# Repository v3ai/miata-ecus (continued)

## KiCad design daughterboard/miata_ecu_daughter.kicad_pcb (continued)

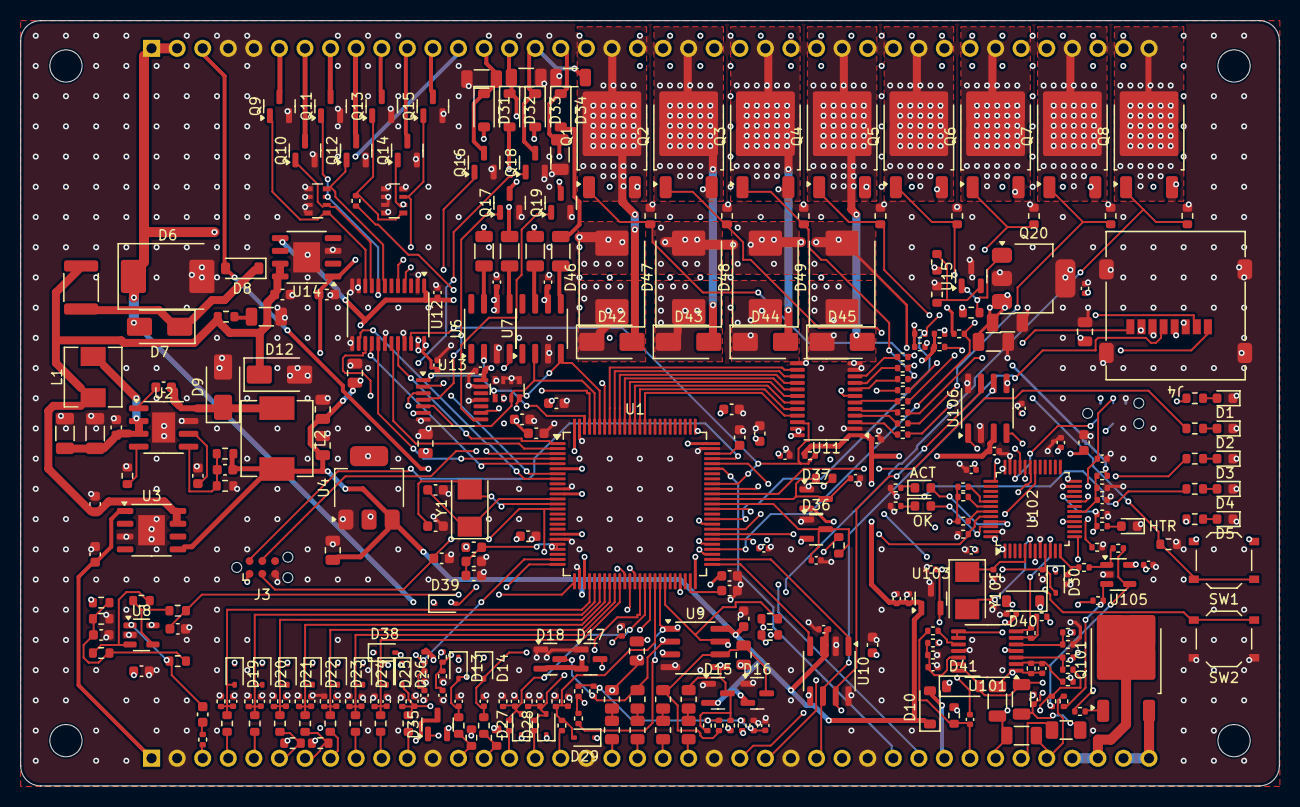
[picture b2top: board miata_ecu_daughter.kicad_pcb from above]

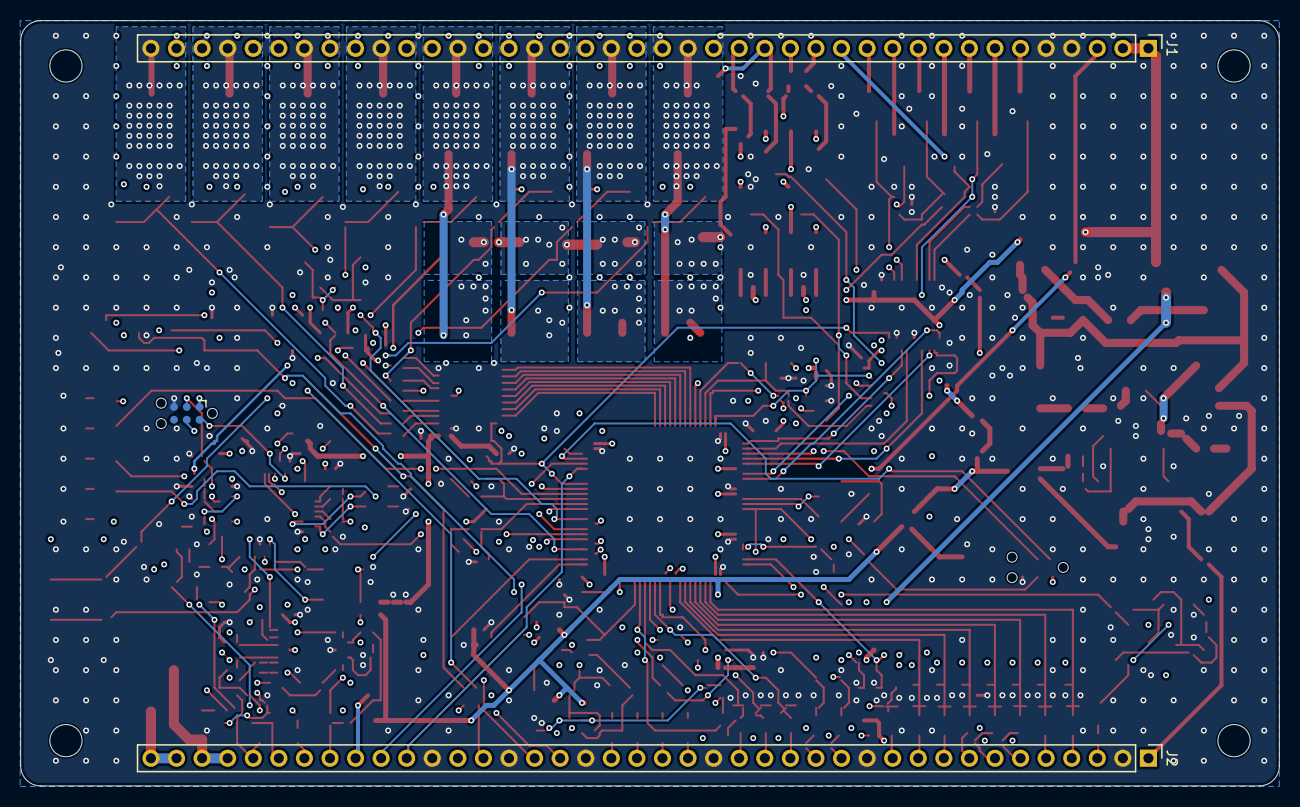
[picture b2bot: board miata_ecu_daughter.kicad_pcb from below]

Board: 6 copper layers, 125.0 x 76.0 mm, 338 parts (3 on the bottom side), 230 nets.

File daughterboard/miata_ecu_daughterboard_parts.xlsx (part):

Group | Qty | Value | Description | Designators | Footprint | LCSC # | JLC type | Notes | Manufacturer | MPN
MCU & support
MCU & support | 7 | 100n |  | C1, C2, C3, C5, C6, C12, C15 | C_0603_1608Metric | C14663 | Basic |  | YAGEO | CC0603KRX7R9BB104
MCU & support | 1 | 100n |  | C4 | C_0402_1005Metric | C1525 | Basic |  | Samsung Electro-Mechanics | CL05B104KO5NNNC
MCU & support | 1 | 10k |  | R1 | R_0603_1608Metric | C25804 | Basic |  | UNI-ROYAL(Uniroyal Elec) | 0603WAF1002T5E
MCU & support | 1 | 1u |  | C11 | C_0603_1608Metric | C15849 | Basic |  | Samsung Electro-Mechanics | CL10A105KB8NNNC
MCU & support | 2 | 2.2u |  | C9, C10 | C_0603_1608Metric | C23630 | Basic |  | Samsung Electro-Mechanics | CL10A225KO8NNNC
MCU & support | 2 | 33p |  | C13, C14 | C_0603_1608Metric | C1663 | Extended |  | Samsung Electro-Mechanics | CL10C330JB8NNNC
MCU & support | 2 | 4.7u |  | C7, C8 | C_0603_1608Metric | C19666 | Basic |  | Samsung Electro-Mechanics | CL10A475KO8NNNC
MCU & support | 1 | 8MHz | 8MHz crystal 5032, 20pF (YXC X50328MSB2GI) | Y1 | Crystal_SMD_5032-2Pin_5.0x3.2mm | C115962 | Extended |  | YXC Crystal Oscillators | X50328MSB2GI
MCU & support | 1 | BLM18PG221 |  | FB1 | L_0603_1608Metric | C80165 | Extended |  | Murata | BLM18PG221SN1D
MCU & support | 1 | BOOT |  | SW1 | SW_Push_1P1T_XKB_TS-1187A | C318884 | Basic |  | XKB Connection | TS-1187A-B-A-B
MCU & support | 1 | RESET |  | SW2 | SW_Push_1P1T_XKB_TS-1187A | C318884 | Basic |  | XKB Connection | TS-1187A-B-A-B
MCU & support | 1 | STM32F407VGT6 | MCU, Cortex-M4F 168MHz, 1MB flash, LQFP-100 | U1 | LQFP-100_14x14mm_P0.5mm | C12345 | Extended |  | STMicroelectronics | STM32F407VGT6
MCU & support | 1 | SWD | Tag-Connect TC2030-NL footprint, nothing to place | J3 | Tag-Connect_TC2030-IDC-NL_2x03_P1.27mm_Vertical |  |  | Not assembled
Status LEDs
Status LEDs | 5 | 1k |  | R2, R3, R4, R5, R6 | R_0603_1608Metric | C21190 | Basic |  | UNI-ROYAL(Uniroyal Elec) | 0603WAF1001T5E
Status LEDs | 1 | BLUE |  | D2 | LED_0603_1608Metric | C2288 | Extended |  | Hubei KENTO Elec | KT-0603B
Status LEDs | 2 | GREEN |  | D1, D5 | LED_0603_1608Metric | C12624 | Extended |  | Hubei KENTO Elec | KT-0603G
Status LEDs | 1 | RED |  | D4 | LED_0603_1608Metric | C2286 | Basic |  | Hubei KENTO Elec | KT-0603R
Status LEDs | 1 | YELLOW |  | D3 | LED_0603_1608Metric | C2287 | Extended |  | Hubei KENTO Elec | KT-0603Y
Power
Power | 1 | 1 |  | R7 | R_0603_1608Metric | C22936 | Basic |  | UNI-ROYAL(Uniroyal Elec) | 0603WAF100KT5E
Power | 1 | 100n |  | C19 | C_0603_1608Metric | C14663 | Basic |  | YAGEO | CC0603KRX7R9BB104
Power | 2 | 100n |  | C28, C29 | C_0402_1005Metric | C1525 | Basic |  | Samsung Electro-Mechanics | CL05B104KO5NNNC
Power | 1 | 10k |  | R8 | R_0603_1608Metric | C25804 | Basic |  | UNI-ROYAL(Uniroyal Elec) | 0603WAF1002T5E
Power | 1 | 10n |  | C20 | C_0603_1608Metric | C57112 | Basic |  | FH(Guangdong Fenghua Advanced Tech) | 0603B103K500NT
Power | 4 | 10u |  | C22, C23, C26, C27 | C_0805_2012Metric | C15850 | Basic |  | Samsung Electro-Mechanics | CL21A106KAYNNNE
Power | 3 | 10u/50V |  | C16, C17, C18 | C_1206_3216Metric | C13585 | Basic |  | Samsung Electro-Mechanics | CL31A106KBHNNNE
Power | 1 | 10uH |  | L2 | L_Sunlord_MWSA0603S | C132141 | Extended |  | Sunlord | MWSA0603S-100MT
Power | 1 | 12k |  | R10 | R_0603_1608Metric | C22790 | Basic |  | UNI-ROYAL(Uniroyal Elec) | 0603WAF1202T5E
Power | 2 | 1u |  | C24, C25 | C_0603_1608Metric | C15849 | Basic |  | Samsung Electro-Mechanics | CL10A105KB8NNNC
Power | 1 | 2.2uH |  | L1 | L_Sunlord_MWSA0503S | C177247 | Extended |  | cjiang (Changjiang Microelectronics Tech) | FXL0530-2R2-M
Power | 1 | 220p |  | C21 | C_0603_1608Metric | C1603 | Basic |  | Samsung Electro-Mechanics | CL10B221KB8NNNC
Power | 2 | 33k |  | R11, R13 | R_0402_1005Metric | C25779 | Basic |  | UNI-ROYAL(Uniroyal Elec) | 0402WGF3302TCE
Power | 2 | 6.8k |  | R12, R14 | R_0402_1005Metric | C25917 | Basic |  | UNI-ROYAL(Uniroyal Elec) | 0402WGF6801TCE
Power | 1 | 68k |  | R9 | R_0603_1608Metric | C23231 | Basic |  | UNI-ROYAL(Uniroyal Elec) | 0603WAF6802T5E
Power | 1 | B360A | 3A 60V Schottky, buck catch diode | D9 | D_SMA | C94193 | Extended |  | Diodes Incorporated | B360A-13-F
Power | 2 | B5819W | 1A 40V Schottky | D8, D10 | D_SOD-123 | C8598 | Extended |  | JSCJ | B5819W SL
Power | 1 | LDL1117S33R |  | U4 | SOT-223-3_TabPin2 | C435835 | Extended |  | STMicroelectronics | LDL1117S33R
Power | 1 | LMR14020 | 40V 2A buck converter, 12V -> 5V | U2 | SOIC-8-1EP_3.9x4.9mm_P1.27mm_EP2.29x3mm | C187824 | Extended |  | Texas Instruments | LMR14020SDDAR
Power | 1 | SMCJ30A | 1500W TVS, load dump | D6 | D_SMC | C224048 | Extended |  | Littelfuse | SMCJ30A
Power | 1 | SS34 | 3A 40V Schottky | D7 | D_SMA | C8678 | Basic |  | MDD(Microdiode Semiconductor) | SS34
Power | 1 | TLS115B0EJ | 5V sensor supply tracker, short-to-battery protected | U3 | Infineon_PG-DSO-8-27_3.9x4.9mm_EP2.65x3mm | C3743696 | Extended |  | Infineon | TLS115B0EJ
Injector / solenoid drivers
Injector / solenoid drivers | 1 | BCP53-16 |  | Q20 | SOT-223 | C85085 | Extended
Injector / solenoid drivers | 1 | VND14NV04 |  | Q101 | TO-252-2 | C2649436 | Extended |  | STMicroelectronics | VND14NV04TR-E
Injector / solenoid drivers | 8 | VND7NV04TR-E |  | Q1, Q2, Q3, Q4, Q5, Q6, Q7, Q8 | TO-252-2 | C155605 | Extended
Injector / solenoid drivers | 11 | ZXMS6004FFTA |  | Q9, Q10, Q11, Q12, Q13, Q14, Q15, Q16, Q17, Q18, Q19 | SOT-23 | C95063 | Extended
Ignition drivers
Ignition drivers | 4 | 100 |  | R15, R16, R17, R18 | R_1206_3216Metric | C17901 | Extended
Ignition drivers | 2 | 1u |  | C34, C35 | C_0402_1005Metric | C52923 | Extended |  | Samsung Electro-Mechanics | CL05A105KA5NQNC
Ignition drivers | 4 | 3.3k |  | R144, R145, R146, R147 | R_1206_3216Metric | C26032 | Extended
Ignition drivers | 1 | 4x10k |  | RN1 | R_Array_Convex_4x0603 | C29718 | Basic |  | UNI-ROYAL(Uniroyal Elec) | 4D03WGJ0103T5E
Ignition drivers | 1 | 74HCT04PW |  | U13 | TSSOP-14_4.4x5mm_P0.65mm | C131317 | Extended
Ignition drivers | 4 | B5819W | 1A 40V Schottky | D31, D32, D33, D34 | D_SOD-123 | C8598 | Extended |  | JSCJ | B5819W SL
Ignition drivers | 1 | BAT54WS |  | D39 | D_SOD-323 | C124205 | Extended |  | Diodes Incorporated | BAT54WS-7-F
Ignition drivers | 1 | Mezz_Power_Out | 1x40 2.54mm male header (power/outputs) | J1 | PinHeader_1x40_P2.54mm_Vertical | C2977586 | Extended |  | ZHOURI | 2.54-1*40
Ignition drivers | 2 | TC4427 | Dual 1.5A driver, 5V logic out for COP smart coils | U6, U7 | SOIC-8_3.9x4.9mm_P1.27mm | C20551 | Extended |  | Microchip | TC4427AEOA713
Knock input
Knock input | 3 | 100k |  | R45, R46, R47 | R_0603_1608Metric | C25803 | Basic |  | UNI-ROYAL(Uniroyal Elec) | 0603WAF1003T5E
Knock input | 1 | 100n |  | C44 | C_0603_1608Metric | C14663 | Basic |  | YAGEO | CC0603KRX7R9BB104
Knock input | 1 | 10k |  | R49 | R_0603_1608Metric | C25804 | Basic |  | UNI-ROYAL(Uniroyal Elec) | 0603WAF1002T5E
Knock input | 1 | 10n |  | C46 | C_0603_1608Metric | C57112 | Basic |  | FH(Guangdong Fenghua Advanced Tech) | 0603B103K500NT
Knock input | 1 | 1u |  | C45 | C_0603_1608Metric | C15849 | Basic |  | Samsung Electro-Mechanics | CL10A105KB8NNNC
Knock input | 1 | 2.2k |  | R138 | R_0402_1005Metric | C25879 | Basic |  | UNI-ROYAL | 0402WGF2201TCE
Knock input | 1 | 330 |  | R50 | R_0603_1608Metric | C23138 | Basic |  | UNI-ROYAL(Uniroyal Elec) | 0603WAF3300T5E
Knock input | 1 | 47k |  | R48 | R_0603_1608Metric | C25819 | Basic |  | UNI-ROYAL(Uniroyal Elec) | 0603WAF4702T5E
Knock input | 1 | LMV321IDBVR | Op-amp, knock sensor gain stage | U8 | SOT-23-5 | C7972 | Extended |  | Texas Instruments | LMV321IDBVR
VR (crank/cam) input
VR (crank/cam) input | 4 | 100k |  | R73, R74, R75, R76 | R_0402_1005Metric | C25741 | Extended |  | UNI-ROYAL(Uniroyal Elec) | 0402WGF1003TCE
VR (crank/cam) input | 1 | 100n |  | C60 | C_0402_1005Metric | C1525 | Basic |  | Samsung Electro-Mechanics | CL05B104KO5NNNC
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
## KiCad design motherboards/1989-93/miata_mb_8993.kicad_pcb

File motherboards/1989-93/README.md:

# Miata ECU motherboard 1989-1993 (NA6), rev 0.11

The motherboard replaces the stock Mazda ECU board inside the **stock ECU case**. It carries:

- the stock harness header;
- the year-independent I/O: the LSU 4.9 wideband sensor connector, IAT, USB-C and the MAP sensor;
- the sockets for the universal daughterboard, which does all the engine control (including the wideband controller).

## Changes in this revision
- Rev 0.11, for daughterboard rev 0.9: the throttle position sensor conversion uses the stock throttle switch plug, as rusEFI's Hellen NA6 and MRE boards do, instead of rev 0.10's separate lead: J6 is gone. Harness pin 1N (the manual cars' idle contact) is no longer wired straight to the sensor 5 V: it goes through R28 (0R, not fitted), so a car with the stock switch no longer shorts the 5 V to ground at every idle (rev 0.10 and earlier did, if 1N is the idle contact as the rusEFI sources say). Pin 2L goes through R29 (0R, fitted) to the spare analog AUX1 as before, or through R30 (0R, not fitted) to the TPS input. For a sensor on the stock plug: fit R28, move R29 to R30. The links are hand-routed into the rev 0.9 copper; nothing else moved.
- Rev 0.10 (replaced by 0.11): J6, a 4-pin connector for a separate TPS lead.
- Rev 0.9, for daughterboard rev 0.9: the daughterboard sits 16 mm lower, centred on the board (42 mm from the top, as up to rev 0.7), with its J1 on its top edge again: JD1 and the upper standoffs HD1/HD2 are back at their rev 0.7 places, JD2, the lower standoffs HD3/HD4, the AUX header J5 (with F4 beside it) and the parts placed against JD2 (CAN termination R1/R6, pull-up options) are 16 mm lower, and the board is routed again. Not compatible with a rev 0.8 daughterboard.
- Rev 0.8, for daughterboard rev 0.8: the harness's sensor 5 V (1N, 2K) and the AUX header pin J5-14 now come from the daughterboard's protected 5 V (V5_EXT, JD1 pin 13, which was a ground pin): a sensor 5 V wire shorted to the battery no longer back-feeds the MAP sensor and the ECU's own 5 V. The MAP sensor keeps its own supply (V5_SENS). The daughterboard outline on the silkscreen is 16 mm taller (125 x 76 mm): its new strip of output drivers overhangs the free area above JD1. D3/D4 (the batch injector clamps) are now SMCJ30A (33.3-36.8 V breakdown) instead of SMCJ40A: the new daughterboard drivers clamp at 40 V minimum, so a 40 V TVS could leave the turn-off energy in a driver; at 30 V the TVS always clamps first. Not-fitted option R27: 4.7k pull-up from the protected 5 V for the manual cars' TPS idle switch on 2L.
- Rev 0.7: LSU heater fuse F1 is a 3 A hold PTC (LUTE 2920L300/30GR, 30 V, 2920 size) instead of the 2 A 1812 part. A cold LSU 4.9 heater draws 1.6-2.3 A rms at the start of the wideband's warm-up, more than the old fuse holds once warm, so it could trip and the controller time out. No 1812 PTC holds 3 A above 8 V.
- Rev 0.6: freewheel diode D1 on the idle valve and D2 on the purge solenoid (2X) to its +12 V feed (the PWM turn-off energy no longer goes into the daughterboard driver); F4 resettable fuse on the AUX +12 V pin J5-15; not-fitted 12 V pull-up options R20-R22 for the VSS / A/C / clutch inputs. INJ1+INJ4 drive 2U and INJ2+INJ3 drive 2V in parallel (R23/R24), with an SMCJ40A clamp per wire (D3/D4), so no driver carries two injectors; 2Y/2Z are only reached through the not-fitted sequential-conversion links R25/R26.
- Rev 0.5: IAT source is now a removable jumper (JP1, 1x3 2.54 mm header + shunt) instead of the R4 / R5 0R links: shunt on EXT (default) reads the IAT connector J3, on STOCK the stock harness sensor; labelled on the silkscreen.
- Rev 0.4: MAP sensor is now the MPX5700AP (absolute, case 867B, one barb; LCSC C90152) instead of the MPX5700DP: new footprint with the real lozenge body and offset barb, holes on the NXP 23.11 mm spacing with 3.3 mm M3 clearance drills.
- Rev 0.3: sensor 5 V now on both 1N (NA6, per the Hellen NA6 map) and 2K; spare low side on 1R (the early cars' BLK/GRN fan-relay wire); 2S left open (it is only used on 94-95).
- Rev 0.2: wideband controller moved to the daughterboard; J5 centred; MAP sensor rotated 90 deg clockwise; LSU connector 6 mm right; SWD header removed; heater fuse now 30 V rated.

## Files
| Path | What |
|---|---|
| `miata_mb_8993.kicad_pro / .kicad_sch / .kicad_pcb` | KiCad 7 project. Root schematic plus three sheets: harness, daughterboard, I/O |
| `miata_mb_8993_schematic.pdf` | Schematic PDF |
| `fab/miata-ecu-motherboard-1989-93-rev0.11_jlcpcb_gerbers.zip`, `fab/miata-ecu-motherboard-1989-93-rev0.11_jlcpcb_bom.csv`, `fab/miata-ecu-motherboard-1989-93-rev0.11_jlcpcb_cpl.csv` | JLC fabrication and assembly files (2 layers, 1.6 mm). The JLC BOM is the SMD parts and USB-C only |
| `fab/miata-ecu-motherboard-1989-93-rev0.11_self_order_bom.csv` | Everything you order and fit yourself: harness header, through-hole connectors, MAP sensor, shunt, standoffs and screws, plus the not-fitted options. Its columns load into LCSC's BOM tool |
| `fab/miata-ecu-motherboard-1989-93-rev0.11_parts_list.csv` | Every part, including the hand-fitted and not-fitted ones |
| `fab/drc_report.txt` | KiCad DRC |
| `ecu_mb.pretty/`, `fp-lib-table` | Project footprints (harness header, MAP sensor lying flat, USB-C, M4 case hole) |
| `renders/` | Top and bottom copper |
| `scripts/` | The design source; `mb_make.sh` rebuilds the whole board |

## Case fit
Stock NA case (same for 1990-95). Outline and holes come from the rusEFI microRusEFI NA plug-and-play board, which fits this case, measured against its known 48-pin header footprint, and from the early Hellen NA6 KiCad board (rev a/b), which uses the same Mazda case outline. H1 is a recessed boss: stack 3 M4 washers under the board.

Board: **154.0 × 161.5 mm**, 1.6 mm. The origin is the top-left corner and y points down, toward the bottom edge.

| Hole | x, y (mm) |
|---|---|
| H1 | 17.0, 7.3 |
| H2 | 137.0, 7.3 |
| H3 | 4.0, 84.0 |
| H4 | 150.0, 84.0 |
| H5 | 4.0, 143.0 |
| H6 | 150.0, 143.0 |

All holes are 4.5 mm plated with a 7 mm pad, tied to GND, for M4 screws. Harness header terminal 1A sits at (39.70, 18.13) mm (lower pin row).

## Harness header
TE **174917-6**, 48 pins: plug 1 = 1A-1V (22 pins), plug 2 = 2A-2Z (26 pins); rusEFI's 1990 page calls the second plug 3A-3Z. TE lists it as not currently available: desolder one from a stock ECU or use a clone. Fitted by hand.

| Pin | Net | Use | Stock function / note |
|---|---|---|---|
| 1B | `VBAT_IN` | ECU power (main relay) | main relay output: ECU power |
| 1C | `VIGN_IN` | switched 12 V sense (wakes the logic supply) | starter (START) signal: battery only while cranking. Not ignition-on: the firmware doesn't use it as ignition sense |
| 1E | `OUT_CEL` | check engine lamp |  |
| 1G | `OUT_IGN1` | ignition 1 (5 V logic) | igniter 1&4 (wasted spark) / COP 1 |
| 1H | `OUT_IGN2` | ignition 2 (5 V logic) | igniter 2&3 (wasted spark) / COP 2 |
| 1J | `OUT_AC` | A/C relay | A/C relay |
| 1L | `OUT_FAN` | fan relay | radiator fan relay |
| 1M | `IN_SW1` | 12 V switch input 1 | vehicle speed sensor |
| 1N | `HARN_1N` |  | manual cars: the stock throttle switch's idle contact (closes to ground at idle). 5 V only through R28 (not fitted), for a 0-5 V sensor on the stock plug |
| 1Q | `IN_SW2` | 12 V switch input 2 | A/C switch |
| 1R | `OUT_LS7` | spare low side | A/C extra cooling fan relay (BLK/GRN) on 1990-91; moved to 1L on later cars |
| 1V | `IN_SW3` | 12 V switch input 3 | clutch switch |
| 2A | `GND` | ground |  |
| 2B | `GND` | ground | power ground |
| 2C | `GND` | ground |  |
| 2D | `GND` | ground | signal ground |
| 2E | `IN_HALL1` | hall input 1 (crank) | CAS crank (SGT, open collector) |
| 2F | `GND` | ground | AFM ground |
| 2G | `IN_HALL2` | hall input 2 (cam) | CAS cam (SGC) |
| 2I | `OUT_TACH` | tach out |  |
| 2K | `V5_EXT` | sensor 5 V reference (out; protected, short-to-battery proof) | 5 V sensor reference (protected harness 5 V) |
| 2L | `HARN_2L` |  | manual cars: the throttle switch's other contact. R29 (fitted) to the spare analog AUX1, or R30 (not fitted) to the TPS input after a sensor conversion |
| 2M | `IN_TPS` | TPS | automatics' TPS signal (a manual car's converted sensor comes in on 2L through R30) |
| 2N | `IN_AUX2` | spare analog 2 | stock narrowband O2 |
| 2O | `IN_AUX3` | spare analog 3 | AFM flap signal |
| 2P | `HARN_IAT` | stock air-temp sensor (JP1 on STOCK) | AFM air temp (IAT jumper JP1 on STOCK to use it) |
| 2Q | `IN_CLT` | coolant temp |  |
| 2T | `OUT_FP` | fuel pump relay | fuel pump relay |
| 2U | `OUT_INJ1` | injector 1 | stock: two injectors on this wire (batch); INJ1 + INJ4 drive it in parallel (R23) |
| 2V | `OUT_INJ2` | injector 2 | stock: the other two injectors (batch); INJ2 + INJ3 in parallel (R24) |
| 2W | `OUT_IACV` | idle air valve |  |
| 2X | `OUT_VVT` | PWM low side (VVT driver) | purge solenoid (VVT driver reused, set as purge / generic PWM) |
| 2Y | `HARN_2Y` |  | empty on manual cars: INJ3 only through R25 (not fitted) after a sequential conversion |
| 2Z | `HARN_2Z` |  | A/T control unit on automatics: INJ4 only through R26 (not fitted), never on an automatic |

Not connected: 1A, 1D, 1F, 1I, 1K, 1O, 1P, 1S, 1T, 1U, 2H, 2J, 2R, 2S.

## Bottom edge, left to right
| Ref | What | Notes |
|---|---|---|
| J2 | LSU 4.9 (Molex Micro-Fit 2×3, right angle) | Pin n = LSU pin n: 1 IP, 2 VM, 3 H−, 4 H+, 5 RT, 6 UN. Heater fed from the main relay through F1 (3 A hold, 30 V, 2920). The controller is on the daughterboard |
| J3 | IAT (Micro-Fit 1×2) | M12×1.5 open-element thermistor, used when the IAT jumper JP1 is on EXT |
| JP1 | IAT source jumper (1×3, 2.54 mm) | Shunt on **2-3 (EXT, default)**: the IAT connector J3. Shunt on **1-2 (STOCK)**: the stock air-temp sensor through the harness (inside the AFM on 1989-97, the MAF on 1999-2005). Set the matching sensor curve in TunerStudio; the pull-up is 2.7 kΩ |
| J4 | USB-C | USB 2.0 device: tuning, logging, DFU |
| U2 | MPX5700AP | Absolute MAP sensor (15-700 kPa, case 867B). Lies flat on 2 × M3, marking side up, leads bent 90° down, the single barb toward the board centre |

**CAN:** R1 + R6 terminate the bus at the ECU end; remove R6 if the bus is terminated elsewhere.

**AUX (J5, 2×8 box header):** what the stock harness has no pins for: COP 3/4, boost, alternator and main-relay outputs, knock input, VR crank/cam inputs, external AFR input, UART, 5 V sensor supply, +12 V and GND.

**Protection (motherboard rev 0.4 / 0.6):** D1 (and D2 where the VVT driver runs a coil) freewheel the PWM valve coils into their own +12 V feed, so the drivers don't absorb the turn-off energy. F4 fuses the AUX +12 V pin (0.5 A hold).

**Switch inputs (R20-R22, not fitted):** the VSS, A/C and clutch inputs read signals that are driven to 12 V. If your car's signal only switches to ground (or is open collector), fit the 4.7 kΩ pull-up for that input. Never fit it for a switch that drives 12 V: the input would always read on.

**Throttle position sensor (manual cars):** the 1989-93 manual cars have no throttle position sensor, only a two-contact switch. The ECU calculates fuel from the MAP sensor, so the car runs without one, but rusEFI then flags the throttle sensor as failed and drops closed-loop idle, throttle-based acceleration fuel and overrun fuel cut. A 0-5 V sensor fits on the stock wiring, as on rusEFI's Hellen NA6 and MRE boards: the switch plug has three wires, the idle contact (1N), ground (2D) and the full-throttle contact (2L), and a sensor needs 5 V, ground and a signal. **Board links:** fit R28 (0R 0805) to put the protected 5 V on 1N, and move the 0R from R29 to R30 so that 2L goes to the TPS input instead of AUX1. Until R28 is fitted, 1N is open: with the stock switch fitted, 5 V on 1N would be shorted to ground at every idle. **Sensor:** a Kia sensor with the same 3-pin Mazda plug (0K01118911 and the others in the self-order BOM) plugs into the stock plug, on a printed mount (Thingiverse 3414132, print in ASA); or Flyin' Miata's TPS upgrade kit. **Before fitting R28,** unplug the switch and check on your car which plug wire reaches 1N, 2L and 2D, and on the sensor which pins are the ends of its track (constant resistance between them at any throttle): those must meet 1N and 2D, and the third (the wiper) 2L. In TunerStudio, calibrate the throttle closed and wide open (a reversed sensor calibrates the same way). **Automatics** already have a sensor on 2M (with its 5 V on 2K): leave R28 and R30 off. Every part is in the self-order BOM.

**Throttle switch contact (R27, not fitted):** on the manual cars 2L is one of the throttle switch's contacts, which closes to ground. Fit the 4.7 kΩ pull-up to the protected 5 V only if you keep the stock switch and want the ECU to read it (on AUX1, through R29); never with a sensor on 2L.

**Sensor 5 V:** the harness's 5 V reference and the AUX header pin J5-14 come from the daughterboard's protected 5 V regulator (V5_EXT; it survives a short to the battery or to ground). The MAP sensor has its own supply (V5_SENS), so a damaged sensor wire doesn't take the MAP reading with it.

**Injectors (1989-93):** the stock harness has two injectors on each of 2U and 2V (about 1.8 A per wire). Two daughterboard drivers share each wire through R23 (INJ1 + INJ4 on 2U) and R24 (INJ2 + INJ3 on 2V); rusEFI's batch mode fires each pair together. D3/D4 (SMCJ30A) clamp each wire at about 37 V, below the drivers' own 40 V minimum clamp, so the drivers never take the turn-off energy. For a sequential conversion (new wires to 2Y/2Z), remove R23/R24, fit R25/R26 and switch the firmware to sequential. **Never fit R26 on an automatic: 2Z goes to the A/T control unit.**

## Assembly
- The daughterboard plugs into JD1/JD2 (8.5 mm sockets) on four M3 × 11 mm standoffs.
- Fitted by hand (all in `fab/miata-ecu-motherboard-1989-93-rev0.11_self_order_bom.csv`): the harness header (salvage from a stock ECU or use a clone), the daughterboard sockets JD1/JD2, the LSU and IAT connectors, the AUX header, the JP1 header and its shunt (EXT or STOCK), the MAP sensor, the standoffs, and any not-fitted option links. JLCPCB fits only the SMD parts and USB-C. USB-C has through-hole shell pegs: check in JLC's quote whether that needs Standard PCBA.
- The case needs cut-outs in its bottom edge for the LSU, IAT, USB-C and MAP hose.

## Still to verify
- The case geometry: hole centres and header 1A position, with calipers on a stock case.
- Your car's fan wiring: early cars switch the fan relay on 1R, later ones on 1L; both are driven (fan and spare outputs).
- LCSC stock for the extended parts (C124412, C127367, C277684, C587650, C3020560, C410772, C46641168, C3406).
- Harness pins 1N and 2L on a 1989-93 car: with the throttle switch unplugged, which plug wire reaches each (the rusEFI sources give 1N = idle contact, 2D = ground, 2L = full-throttle contact). Do this before fitting R28.
- The TPS conversion on a manual car: the sensor and mount against your throttle body, and the sensor's output across the throttle travel (calibrate closed and wide open in TunerStudio).

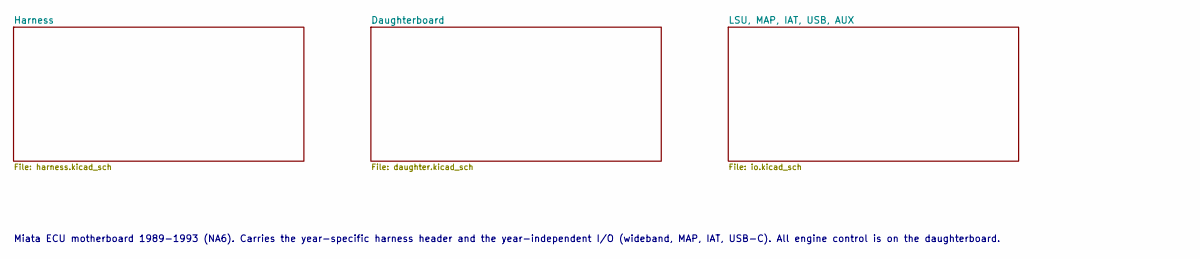
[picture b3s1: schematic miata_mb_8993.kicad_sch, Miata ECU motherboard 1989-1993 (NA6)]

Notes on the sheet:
Miata ECU motherboard 1989-1993 (NA6). Carries the year-specific harness header and the year-independent I/O (wideband, MAP, IAT, USB-C). All engine control is on the daughterboard.

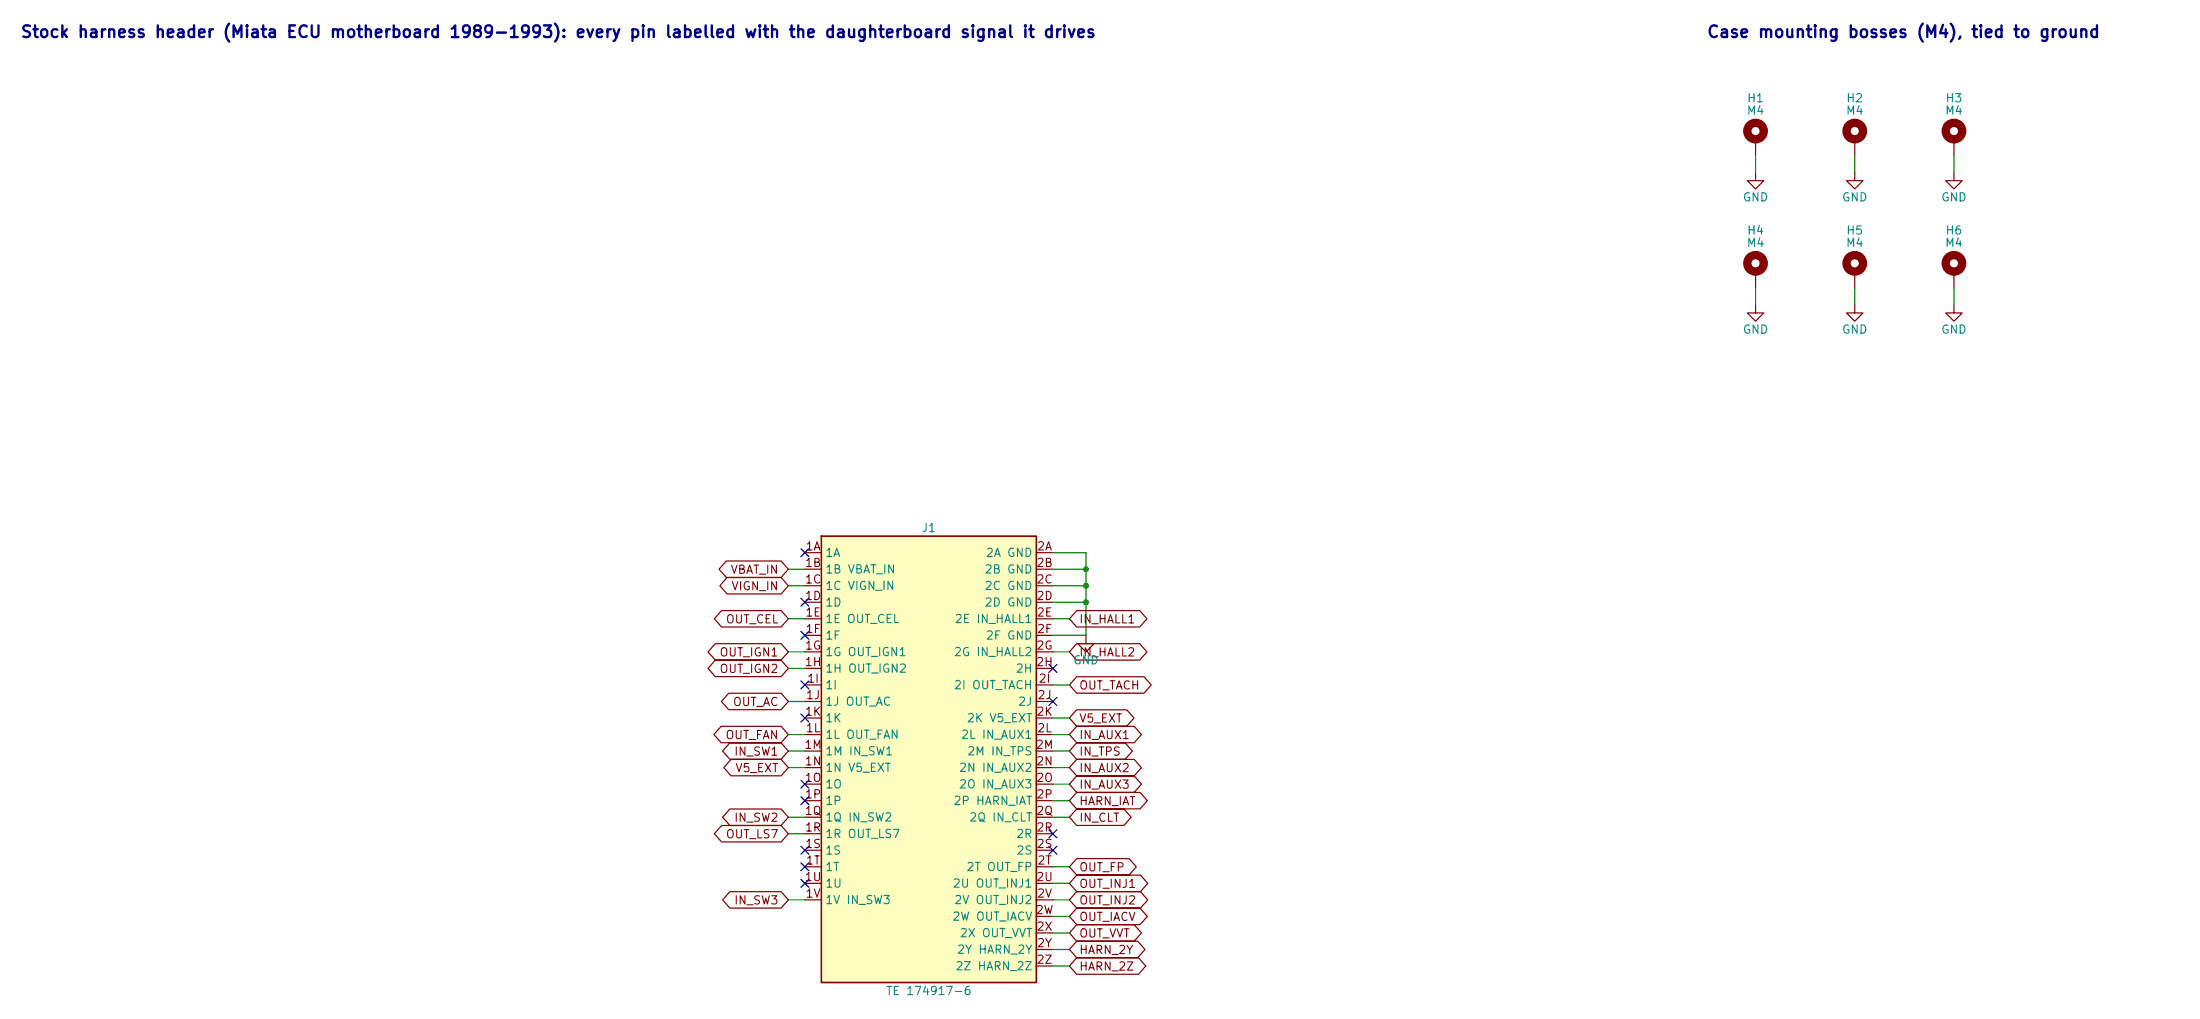
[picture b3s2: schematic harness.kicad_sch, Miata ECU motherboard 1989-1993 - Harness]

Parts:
H1, H2, H3, H4, H5, H6: M4; MountingHole_M4_4.5mm_Pad7
J1: TE 174917-6; TE_174917-6_48P

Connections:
GND: H1.1, H2.1, H3.1, H4.1, H5.1, H6.1, J1.2A (2A GND), J1.2B (2B GND), J1.2C (2C GND), J1.2D (2D GND), J1.2F (2F GND); also elsewhere on the board
HARN_2Y: J1.2Y (2Y HARN_2Y); also elsewhere on the board
HARN_2Z: J1.2Z (2Z HARN_2Z); also elsewhere on the board
HARN_IAT: J1.2P (2P HARN_IAT); also elsewhere on the board
IN_AUX1: J1.2L (2L IN_AUX1); also elsewhere on the board
IN_AUX2: J1.2N (2N IN_AUX2); also elsewhere on the board
IN_AUX3: J1.2O (2O IN_AUX3); also elsewhere on the board
IN_CLT: J1.2Q (2Q IN_CLT); also elsewhere on the board
IN_HALL1: J1.2E (2E IN_HALL1); also elsewhere on the board
IN_HALL2: J1.2G (2G IN_HALL2); also elsewhere on the board
IN_SW1: J1.1M (1M IN_SW1); also elsewhere on the board
IN_SW2: J1.1Q (1Q IN_SW2); also elsewhere on the board
IN_SW3: J1.1V (1V IN_SW3); also elsewhere on the board
IN_TPS: J1.2M (2M IN_TPS); also elsewhere on the board
OUT_AC: J1.1J (1J OUT_AC); also elsewhere on the board
OUT_CEL: J1.1E (1E OUT_CEL); also elsewhere on the board
OUT_FAN: J1.1L (1L OUT_FAN); also elsewhere on the board
OUT_FP: J1.2T (2T OUT_FP); also elsewhere on the board
OUT_IACV: J1.2W (2W OUT_IACV); also elsewhere on the board
OUT_IGN1: J1.1G (1G OUT_IGN1); also elsewhere on the board
OUT_IGN2: J1.1H (1H OUT_IGN2); also elsewhere on the board
OUT_INJ1: J1.2U (2U OUT_INJ1); also elsewhere on the board
OUT_INJ2: J1.2V (2V OUT_INJ2); also elsewhere on the board
OUT_LS7: J1.1R (1R OUT_LS7); also elsewhere on the board
OUT_TACH: J1.2I (2I OUT_TACH); also elsewhere on the board
OUT_VVT: J1.2X (2X OUT_VVT); also elsewhere on the board
V5_EXT: J1.1N (1N V5_EXT), J1.2K (2K V5_EXT); also elsewhere on the board
VBAT_IN: J1.1B (1B VBAT_IN); also elsewhere on the board
VIGN_IN: J1.1C (1C VIGN_IN); also elsewhere on the board

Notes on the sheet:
Stock harness header (Miata ECU motherboard 1989-1993): every pin labelled with the daughterboard signal it drives
Case mounting bosses (M4), tied to ground

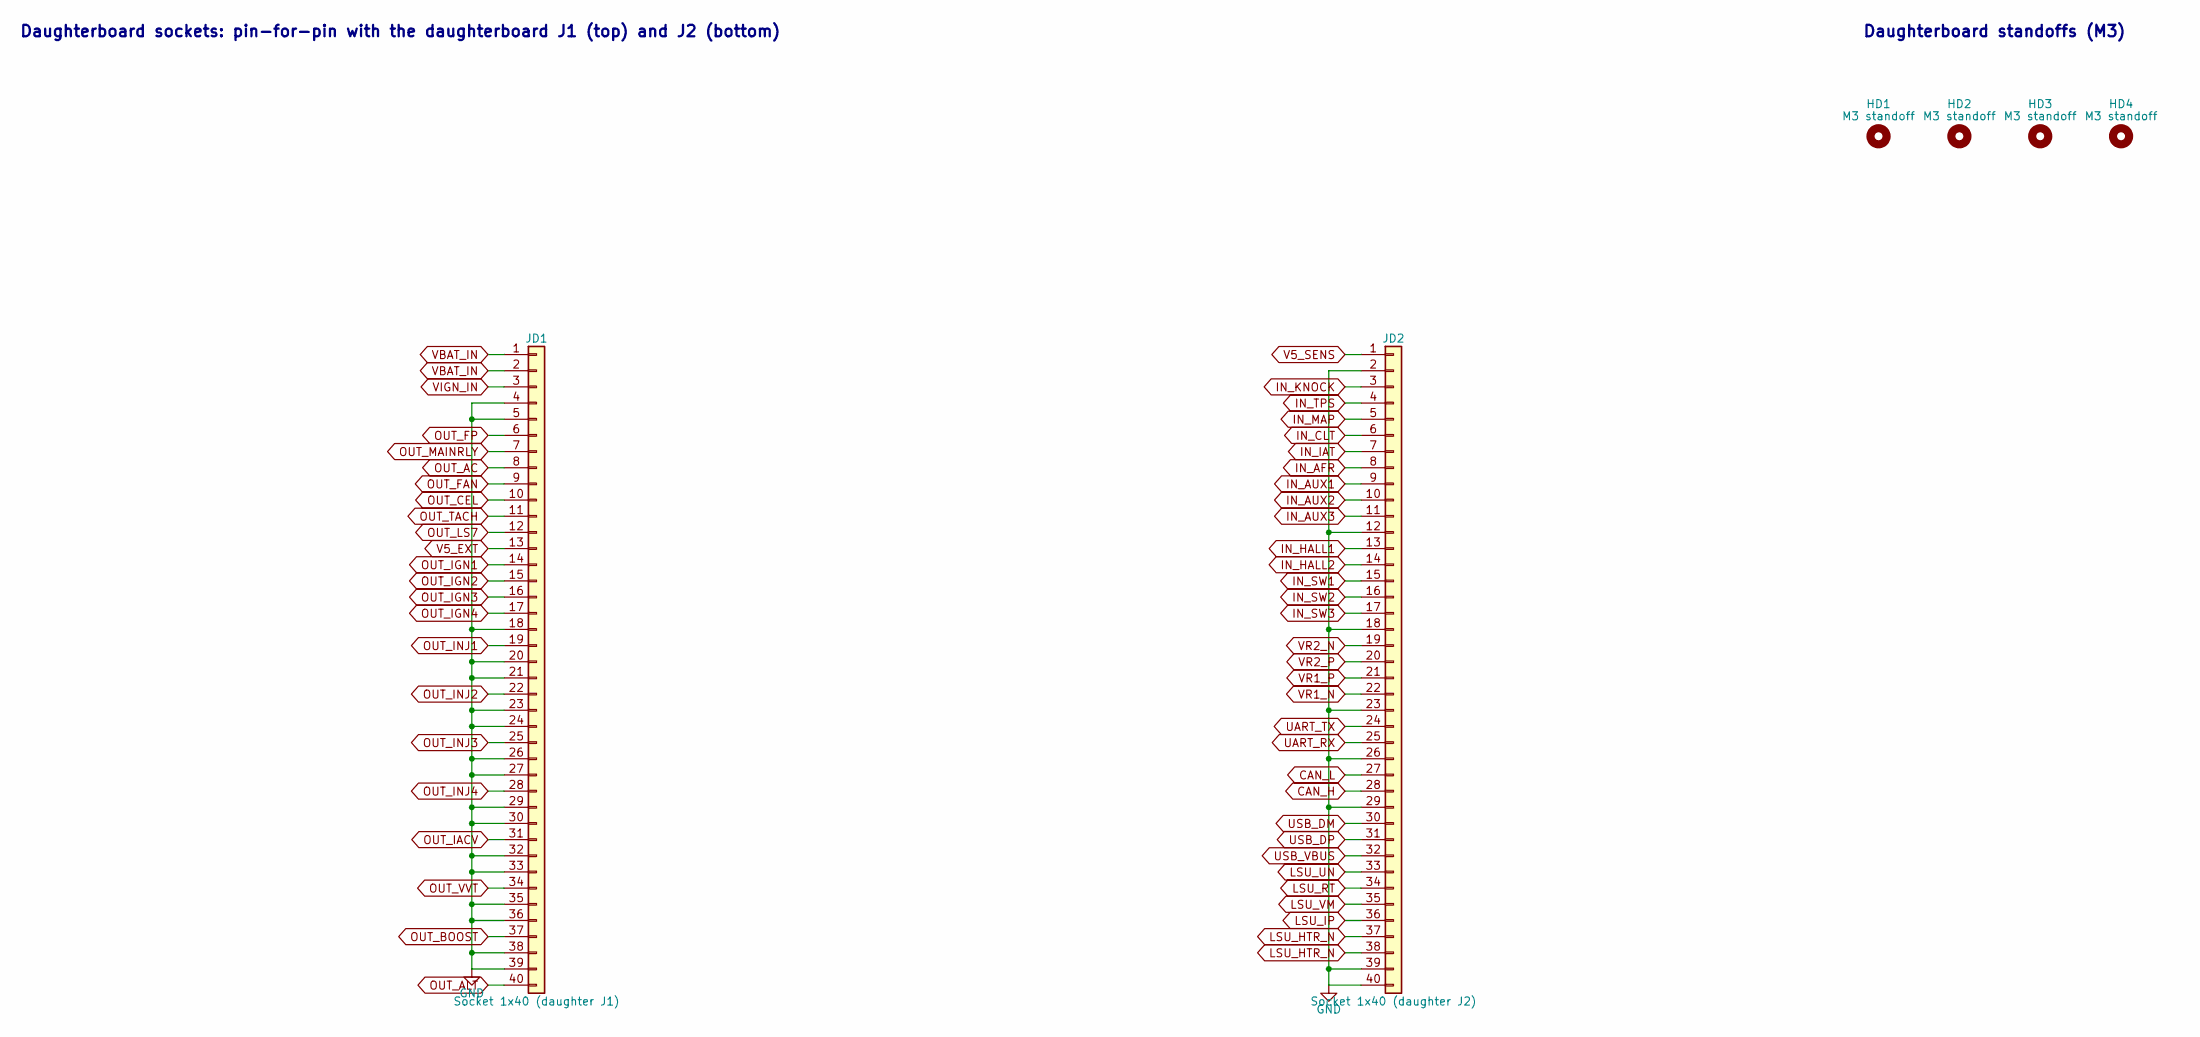
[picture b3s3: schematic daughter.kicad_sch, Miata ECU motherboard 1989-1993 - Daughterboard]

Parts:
HD1, HD2, HD3, HD4: M3 standoff; MountingHole_3.2mm_M3
JD1: Socket 1x40 (daughter J1); PinSocket_1x40_P2.54mm_Vertical; LCSC C124412
JD2: Socket 1x40 (daughter J2); PinSocket_1x40_P2.54mm_Vertical; LCSC C124412

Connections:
CAN_H: JD2.28; also elsewhere on the board
CAN_L: JD2.27; also elsewhere on the board
GND: JD1.4, JD1.5, JD1.18, JD1.20, JD1.21, JD1.23, JD1.24, JD1.26, JD1.27, JD1.29, JD1.30, JD1.32, JD1.33, JD1.35, JD1.36, JD1.38, JD1.39, JD2.2, JD2.12, JD2.18, JD2.23, JD2.26, JD2.29, JD2.39, JD2.40; also elsewhere on the board
IN_AFR: JD2.8; also elsewhere on the board
IN_AUX1: JD2.9; also elsewhere on the board
IN_AUX2: JD2.10; also elsewhere on the board
IN_AUX3: JD2.11; also elsewhere on the board
IN_CLT: JD2.6; also elsewhere on the board
IN_HALL1: JD2.13; also elsewhere on the board
IN_HALL2: JD2.14; also elsewhere on the board
IN_IAT: JD2.7; also elsewhere on the board
IN_KNOCK: JD2.3; also elsewhere on the board
IN_MAP: JD2.5; also elsewhere on the board
IN_SW1: JD2.15; also elsewhere on the board
IN_SW2: JD2.16; also elsewhere on the board
IN_SW3: JD2.17; also elsewhere on the board
IN_TPS: JD2.4; also elsewhere on the board
LSU_HTR_N: JD2.37, JD2.38; also elsewhere on the board
LSU_IP: JD2.36; also elsewhere on the board
LSU_RT: JD2.34; also elsewhere on the board
LSU_UN: JD2.33; also elsewhere on the board
LSU_VM: JD2.35; also elsewhere on the board
OUT_AC: JD1.8; also elsewhere on the board
OUT_ALT: JD1.40; also elsewhere on the board
OUT_BOOST: JD1.37; also elsewhere on the board
OUT_CEL: JD1.10; also elsewhere on the board
OUT_FAN: JD1.9; also elsewhere on the board
OUT_FP: JD1.6; also elsewhere on the board
OUT_IACV: JD1.31; also elsewhere on the board
OUT_IGN1: JD1.14; also elsewhere on the board
OUT_IGN2: JD1.15; also elsewhere on the board
OUT_IGN3: JD1.16; also elsewhere on the board
OUT_IGN4: JD1.17; also elsewhere on the board
OUT_INJ1: JD1.19; also elsewhere on the board
OUT_INJ2: JD1.22; also elsewhere on the board
OUT_INJ3: JD1.25; also elsewhere on the board
OUT_INJ4: JD1.28; also elsewhere on the board
OUT_LS7: JD1.12; also elsewhere on the board
OUT_MAINRLY: JD1.7; also elsewhere on the board
OUT_TACH: JD1.11; also elsewhere on the board
OUT_VVT: JD1.34; also elsewhere on the board
UART_RX: JD2.25; also elsewhere on the board
UART_TX: JD2.24; also elsewhere on the board
USB_DM: JD2.30; also elsewhere on the board
USB_DP: JD2.31; also elsewhere on the board
USB_VBUS: JD2.32; also elsewhere on the board
V5_EXT: JD1.13; also elsewhere on the board
V5_SENS: JD2.1; also elsewhere on the board
VBAT_IN: JD1.1, JD1.2; also elsewhere on the board
VIGN_IN: JD1.3; also elsewhere on the board
VR1_N: JD2.22; also elsewhere on the board
VR1_P: JD2.21; also elsewhere on the board
VR2_N: JD2.19; also elsewhere on the board
VR2_P: JD2.20; also elsewhere on the board

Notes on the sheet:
Daughterboard sockets: pin-for-pin with the daughterboard J1 (top) and J2 (bottom)
Daughterboard standoffs (M3)

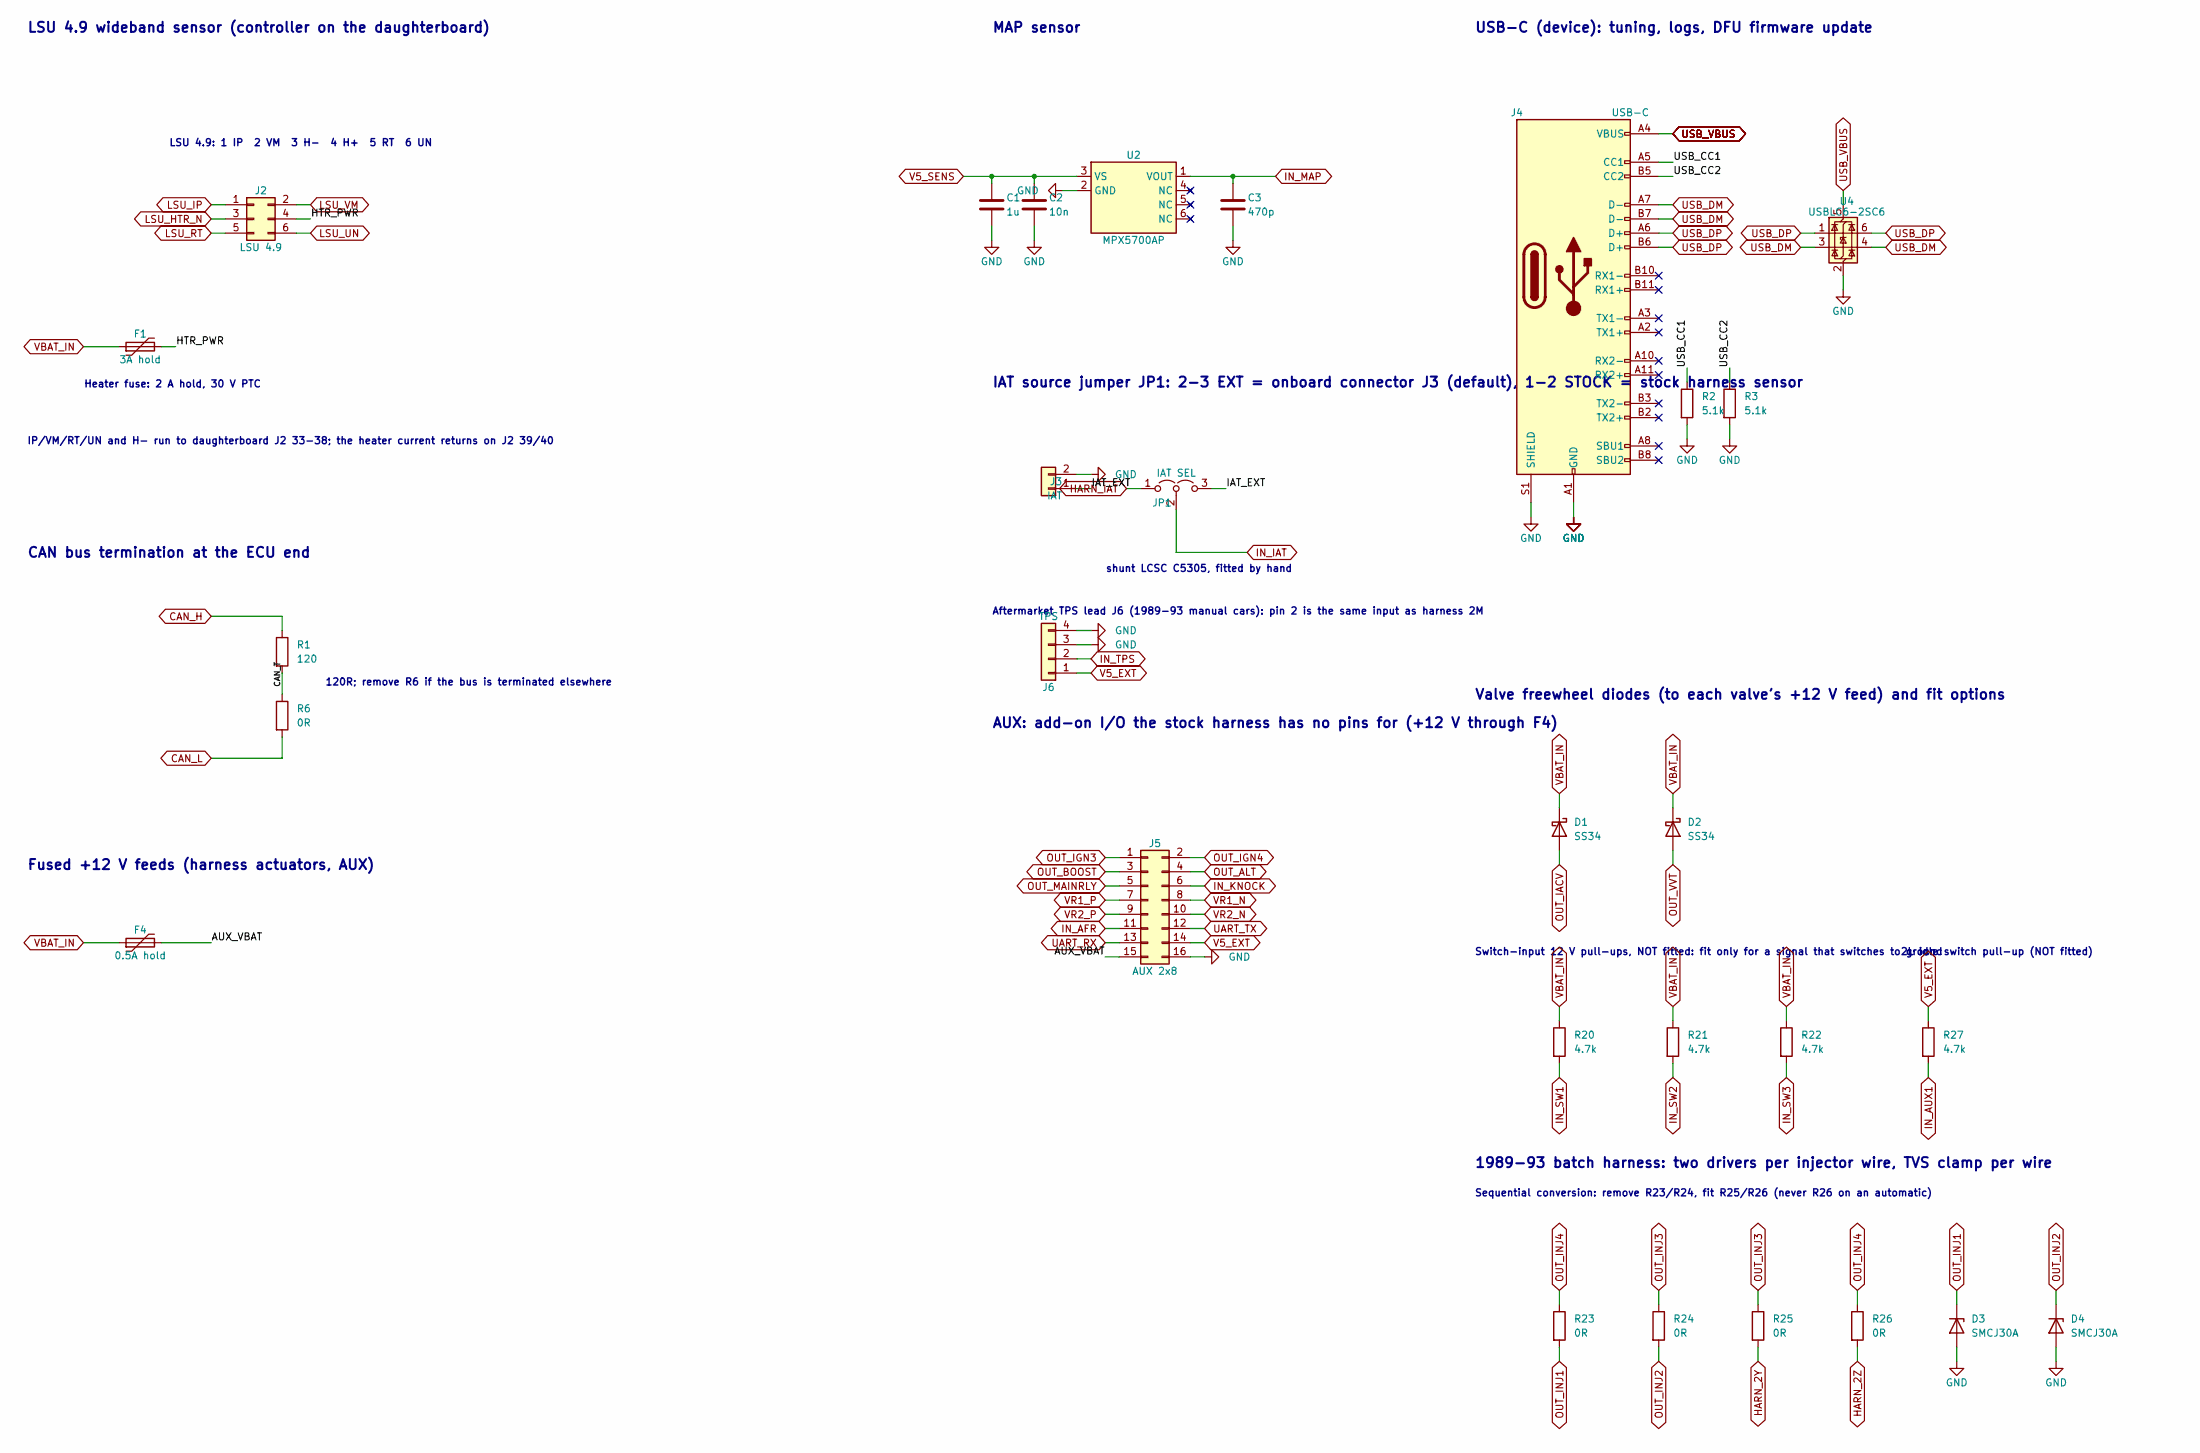
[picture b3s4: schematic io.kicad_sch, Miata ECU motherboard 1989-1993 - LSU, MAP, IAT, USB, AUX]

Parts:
C1: 1u; C_0603_1608Metric; LCSC C15849
C2: 10n; C_0603_1608Metric; LCSC C57112
C3: 470p; C_0603_1608Metric; LCSC C1620
D1, D2: SS34; D_SMA; LCSC C8678
D3, D4: SMCJ30A; D_SMC; LCSC C224048
F1: 3A hold; Fuse_2920_7451Metric; LCSC C22446884
F4: 0.5A hold; Fuse_1206_3216Metric; LCSC C70077
J2: LSU 4.9; Molex_Micro-Fit_3.0_43045-0600_2x03_P3.00mm_Horizontal; LCSC C127367
J3: IAT; Molex_Micro-Fit_3.0_43650-0200_1x02_P3.00mm_Horizontal; LCSC C587650
J4: USB-C; USB_C_GCT_USB4105_16P; LCSC C3020560
J5: AUX 2x8; IDC-Header_2x08_P2.54mm_Vertical; LCSC C3406
J6: TPS; Molex_Micro-Fit_3.0_43650-0400_1x04_P3.00mm_Horizontal; LCSC C277684
JP1: IAT SEL; PinHeader_1x03_P2.54mm_Vertical; LCSC C49257
R1: 120; R_0603_1608Metric; LCSC C22787
R2, R3: 5.1k; R_0603_1608Metric; LCSC C23186
R6: 0R; R_0603_1608Metric; LCSC C21189
R20, R21, R22, R27: 4.7k; R_0603_1608Metric
R23, R24: 0R; R_0805_2012Metric; LCSC C17477
R25, R26: 0R; R_0805_2012Metric
U2: MPX5700AP; MPX5700AP_867B_Flat; LCSC C90152
U4: USBLC6-2SC6; SOT-23-6; LCSC C7519

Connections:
/LSU, MAP, IAT, USB, AUX/AUX_VBAT: F4.2, J5.15
/LSU, MAP, IAT, USB, AUX/CAN_T: R1.2, R6.1
/LSU, MAP, IAT, USB, AUX/HTR_PWR: F1.2, J2.4
/LSU, MAP, IAT, USB, AUX/IAT_EXT: J3.1, JP1.3 (B)
/LSU, MAP, IAT, USB, AUX/USB_CC1: J4.A5 (CC1), R2.1
/LSU, MAP, IAT, USB, AUX/USB_CC2: J4.B5 (CC2), R3.1
CAN_H: R1.1; also elsewhere on the board
CAN_L: R6.2; also elsewhere on the board
GND: C1.2, C2.2, C3.2, D3.2 (A), D4.2 (A), J3.2, J4.A1 (GND), J4.A12 (GND), J4.B1 (GND), J4.B12 (GND), J4.S1 (SHIELD), J5.16, J6.3, J6.4, R2.2, R3.2, U2.2 (GND), U4.2 (GND); also elsewhere on the board
HARN_2Y: R25.2; also elsewhere on the board
HARN_2Z: R26.2; also elsewhere on the board
HARN_IAT: JP1.1 (A); also elsewhere on the board
IN_AFR: J5.11; also elsewhere on the board
IN_AUX1: R27.2; also elsewhere on the board
IN_IAT: JP1.2 (C); also elsewhere on the board
IN_KNOCK: J5.6; also elsewhere on the board
IN_MAP: C3.1, U2.1 (VOUT); also elsewhere on the board
IN_SW1: R20.2; also elsewhere on the board
IN_SW2: R21.2; also elsewhere on the board
IN_SW3: R22.2; also elsewhere on the board
IN_TPS: J6.2; also elsewhere on the board
LSU_HTR_N: J2.3; also elsewhere on the board
LSU_IP: J2.1; also elsewhere on the board
LSU_RT: J2.5; also elsewhere on the board
LSU_UN: J2.6; also elsewhere on the board
LSU_VM: J2.2; also elsewhere on the board
OUT_ALT: J5.4; also elsewhere on the board
OUT_BOOST: J5.3; also elsewhere on the board
OUT_IACV: D1.2 (A); also elsewhere on the board
OUT_IGN3: J5.1; also elsewhere on the board
OUT_IGN4: J5.2; also elsewhere on the board
OUT_INJ1: D3.1 (K), R23.2; also elsewhere on the board
OUT_INJ2: D4.1 (K), R24.2; also elsewhere on the board
OUT_INJ3: R24.1, R25.1; also elsewhere on the board
OUT_INJ4: R23.1, R26.1; also elsewhere on the board
OUT_MAINRLY: J5.5; also elsewhere on the board
OUT_VVT: D2.2 (A); also elsewhere on the board
UART_RX: J5.13; also elsewhere on the board
UART_TX: J5.12; also elsewhere on the board
USB_DM: J4.A7 (D-), J4.B7 (D-), U4.3 (I/O2), U4.4 (I/O2); also elsewhere on the board
USB_DP: J4.A6 (D+), J4.B6 (D+), U4.1 (I/O1), U4.6 (I/O1); also elsewhere on the board
USB_VBUS: J4.A4 (VBUS), J4.A9 (VBUS), J4.B4 (VBUS), J4.B9 (VBUS), U4.5 (VBUS); also elsewhere on the board
V5_EXT: J5.14, J6.1, R27.1; also elsewhere on the board
V5_SENS: C1.1, C2.1, U2.3 (VS); also elsewhere on the board
VBAT_IN: D1.1 (K), D2.1 (K), F1.1, F4.1, R20.1, R21.1, R22.1; also elsewhere on the board
VR1_N: J5.8; also elsewhere on the board
VR1_P: J5.7; also elsewhere on the board
VR2_N: J5.10; also elsewhere on the board
VR2_P: J5.9; also elsewhere on the board

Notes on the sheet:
LSU 4.9 wideband sensor (controller on the daughterboard)
LSU 4.9: 1 IP 2 VM 3 H- 4 H+ 5 RT 6 UN
IP/VM/RT/UN and H- run to daughterboard J2 33-38; the heater current returns on J2 39/40
Heater fuse: 2 A hold, 30 V PTC
CAN bus termination at the ECU end
120R; remove R6 if the bus is terminated elsewhere
MAP sensor
IAT source jumper JP1: 2-3 EXT = onboard connector J3 (default), 1-2 STOCK = stock harness sensor
shunt LCSC C5305, fitted by hand
Aftermarket TPS lead J6 (1989-93 manual cars): pin 2 is the same input as harness 2M
USB-C (device): tuning, logs, DFU firmware update
Fused +12 V feeds (harness actuators, AUX)
AUX: add-on I/O the stock harness has no pins for (+12 V through F4)
Valve freewheel diodes (to each valve's +12 V feed) and fit options
Switch-input 12 V pull-ups, NOT fitted: fit only for a signal that switches to ground
2L idle switch pull-up (NOT fitted)
1989-93 batch harness: two drivers per injector wire, TVS clamp per wire
Sequential conversion: remove R23/R24, fit R25/R26 (never R26 on an automatic)
